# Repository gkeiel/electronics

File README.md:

# Electronics circuits

A repository with codes, schematic diagrams and simulations of electronic circuits. Each project has its own folder.

The following projects are available:
- [voltage difference detector](./voltage_difference_detector)
- [voltage_signal_conditioner](./voltage_signal_conditioner)
- [voltage source inverter 3-phase SPWM](./voltage_source_inverter_3ph_SPWM)

## Voltage difference detector

A printed circuit board (PCB) design for a voltage difference detector between two input voltages, originally developed for voltage source inverters (VSIs) in parallelism applications. Both the schematic design (.sch) and board layout (.brd) were developed in EAGLE software.

<div align="center">

</div>

## Voltage signal conditioner

A printed circuit board (PCB) design for a voltage sensor and signal conditioner, primarily developed for voltage source inverter (VSI) applications. Both the schematic design (.sch) and board layout (.brd) were developed in EAGLE software.

<div align="center">

</div>

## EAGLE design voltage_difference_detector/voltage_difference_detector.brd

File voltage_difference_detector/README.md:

# Voltage difference detector

A printed circuit board (PCB) design for a voltage difference detector between two input voltages, originally developed for voltage source inverters (VSIs) paralleling applications. Both the schematic design (.sch) and board layout (.brd) were developed in EAGLE software.

Being specified for two 127 V sinusoidal inputs, it contains a circuit with a differential amplifier and a comparator. It calculates the instantaneous voltage difference between the inputs, which is proportional to both phase shift and amplitude of the signals, and compares it with an adjustable threshold. If the threshold is exceeded, the comparator activates a relay and a transistor that retains its current state until a reset button is pressed.

<div align="center">

</div>

##

The figures presented in the sequence show stages involved in manufacturing the PCB and its final destination on a panel for VSI control purposes.

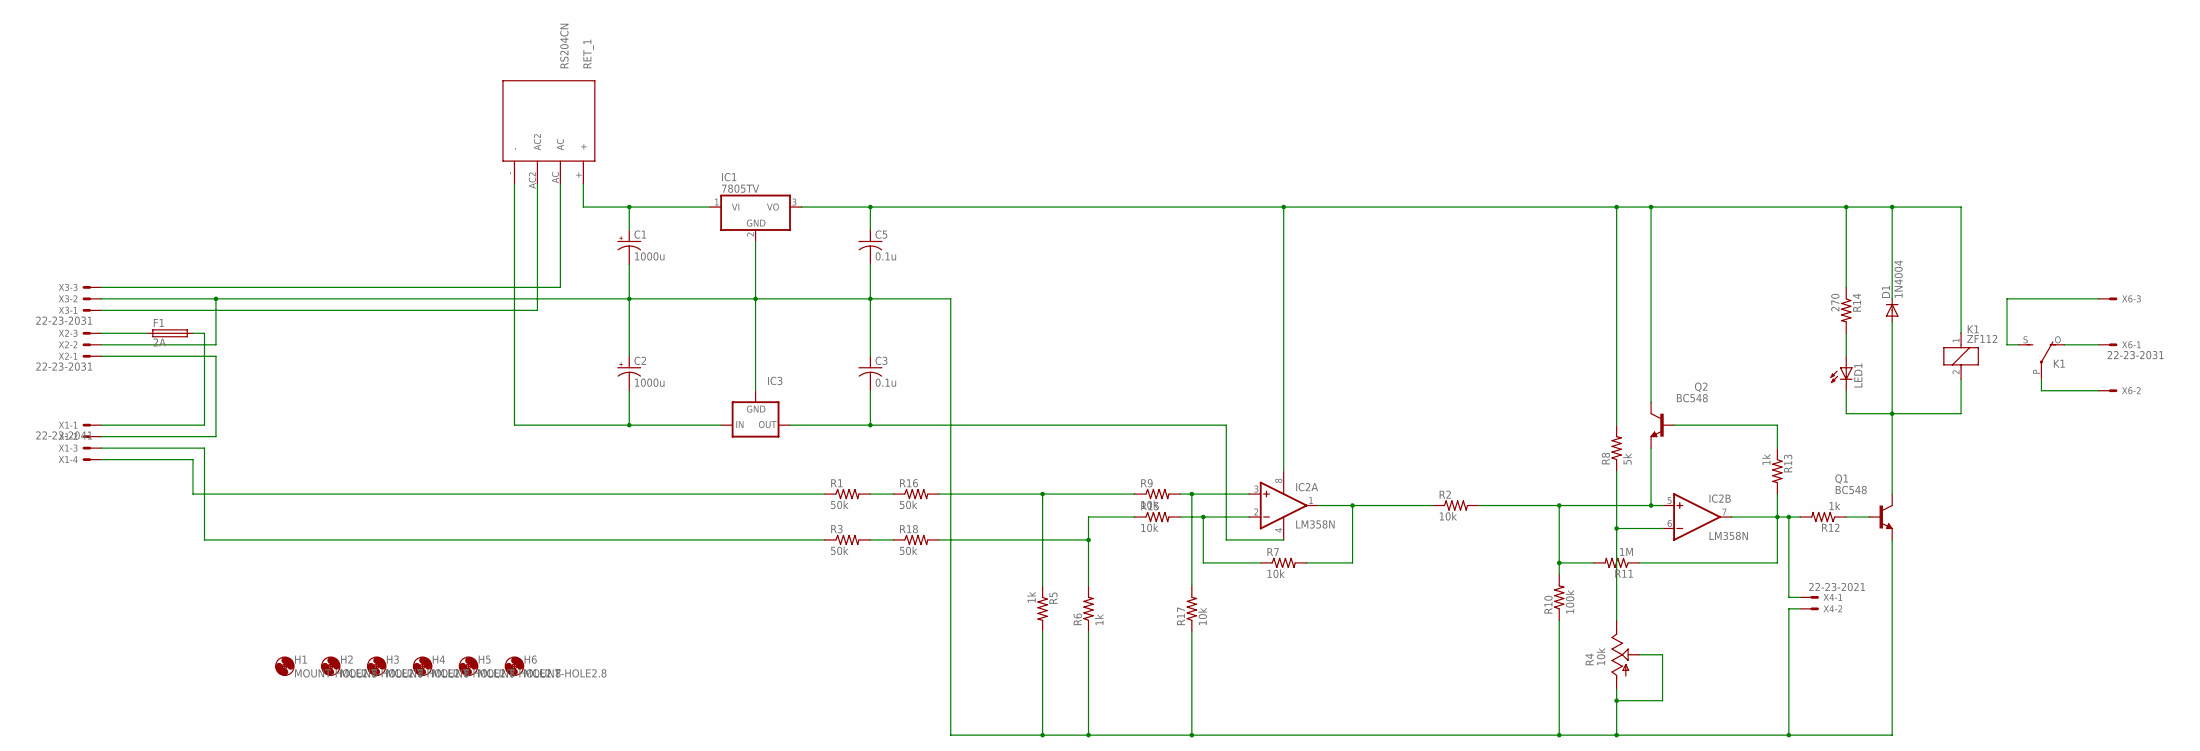
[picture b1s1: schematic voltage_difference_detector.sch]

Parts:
C1, C2: 1000u; E5-10,5
C3, C5: 0.1u; C050-024X044
D1: 1N4004; DO41-10
F1: 2A; SH22,5
H1, H2, H3, H4, H5, H6: MOUNT-HOLE2.8; 2,8
IC1: 7805TV; TO220V
IC2: LM358N; DIL08
IC3: 79XXS
K1: ZF112
LED1: LED3MM
Q1, Q2: BC548; TO92-EBC
R1, R3, R16, R18: 50k; 0204/7
R2, R7, R9, R15, R17: 10k; 0204/7
R4: 10k; RJ9W
R5, R6, R12, R13: 1k; 0204/7
R8: 5k; 0204/7
R10: 100k; 0204/7
R11: 1M; 0204/7
R14: 270; 0204/7
RET_1: RS204CN; SIP
X1: 22-23-2041
X2, X3, X6: 22-23-2031
X4: 22-23-2021

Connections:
GND: C1.-, C2.+, C3.1, C5.2, IC1.2 (GND), IC3.GND, Q1.E, R4.A, R4.S, R5.2, R6.1, R10.1, R17.1, X2.2, X3.2, X4.2
unnamed: C2.-, IC3.IN, RET_1.-
unnamed: IC2.5 (+IN), Q2.E, R2.2, R10.2, R11.2
unnamed: IC2.1 (OUT), R2.1, R7.2
unnamed: RET_1.AC, X3.3
unnamed: R5.1, R9.1, R16.2
unnamed: F1.2, X1.1
unnamed: C1.+, IC1.1 (VI), RET_1.+
unnamed: R1.2, R16.1
unnamed: IC2.2 (-IN), R7.1, R15.2
unnamed: IC2.6 (-IN), R4.E, R8.1
unnamed: IC2.7 (OUT), R11.1, R12.2, R13.2, X4.1
unnamed: Q1.B, R12.1
unnamed: Q2.B, R13.1
unnamed: R6.2, R15.1, R18.2
unnamed: D1.A, K1.2, LED1.K (C), Q1.C
unnamed: R1.1, X1.4
unnamed: R3.1, X1.3
unnamed: RET_1.AC2, X3.1
unnamed: C3.2, IC2.4 (V-), IC3.OUT
unnamed: R3.2, R18.1
unnamed: LED1.A, R14.2
unnamed: X1.2, X2.1
unnamed: K1.O, X6.1
unnamed: K1.P, X6.2
unnamed: K1.S, X6.3
unnamed: IC2.3 (+IN), R9.2, R17.2
unnamed: F1.1, X2.3
VCC: C5.1, D1.C, IC1.3 (VO), IC2.8 (V+), K1.1, Q2.C, R8.2, R14.1

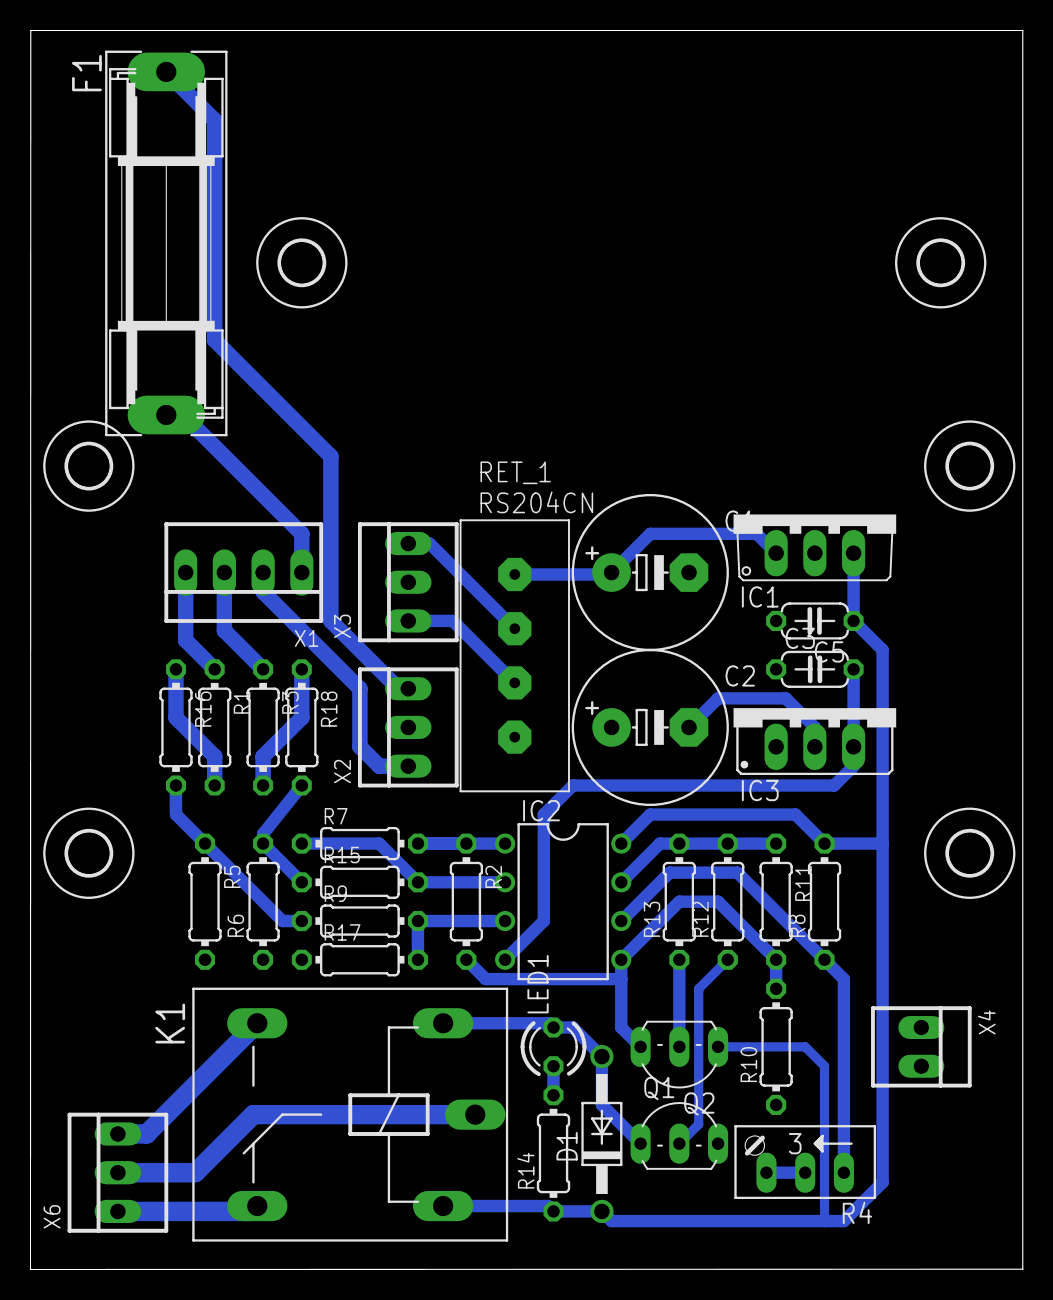
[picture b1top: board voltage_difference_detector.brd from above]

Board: 2 copper layers, 65.1 x 81.3 mm, 43 parts (0 on the bottom side), 29 nets.

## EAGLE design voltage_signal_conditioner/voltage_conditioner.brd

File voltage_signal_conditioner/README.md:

# Voltage signal conditioner

A simple yet functional printed circuit board (PCB) design for a voltage sensor and signal conditioner, primarily developed for voltage source inverter (VSI) applications. Both the schematic design (.sch) and board layout (.brd) were developed in EAGLE software.

Being specified for an 127 V RMS voltage, it accepts a maximum amplitude of 200 V. According to the schematic diagram, it contains a voltage divider at the input with a trimmer for fine adjustment, a Zener limiter to limit voltage arround 10 V, and an isolation amplifier ISO124 integrated circuit (IC) powered with two independent voltage sources. The output has a jumper allowing the selection of RC filtering on the signal.

<div align="center">

</div>

##

The figures presented in the sequence show stages involved in manufacturing the PCB and its final destination on an electirc panel used for control purposes.

<div align="center">

</div>

<div align="center">

</div>

<div align="center">

</div>

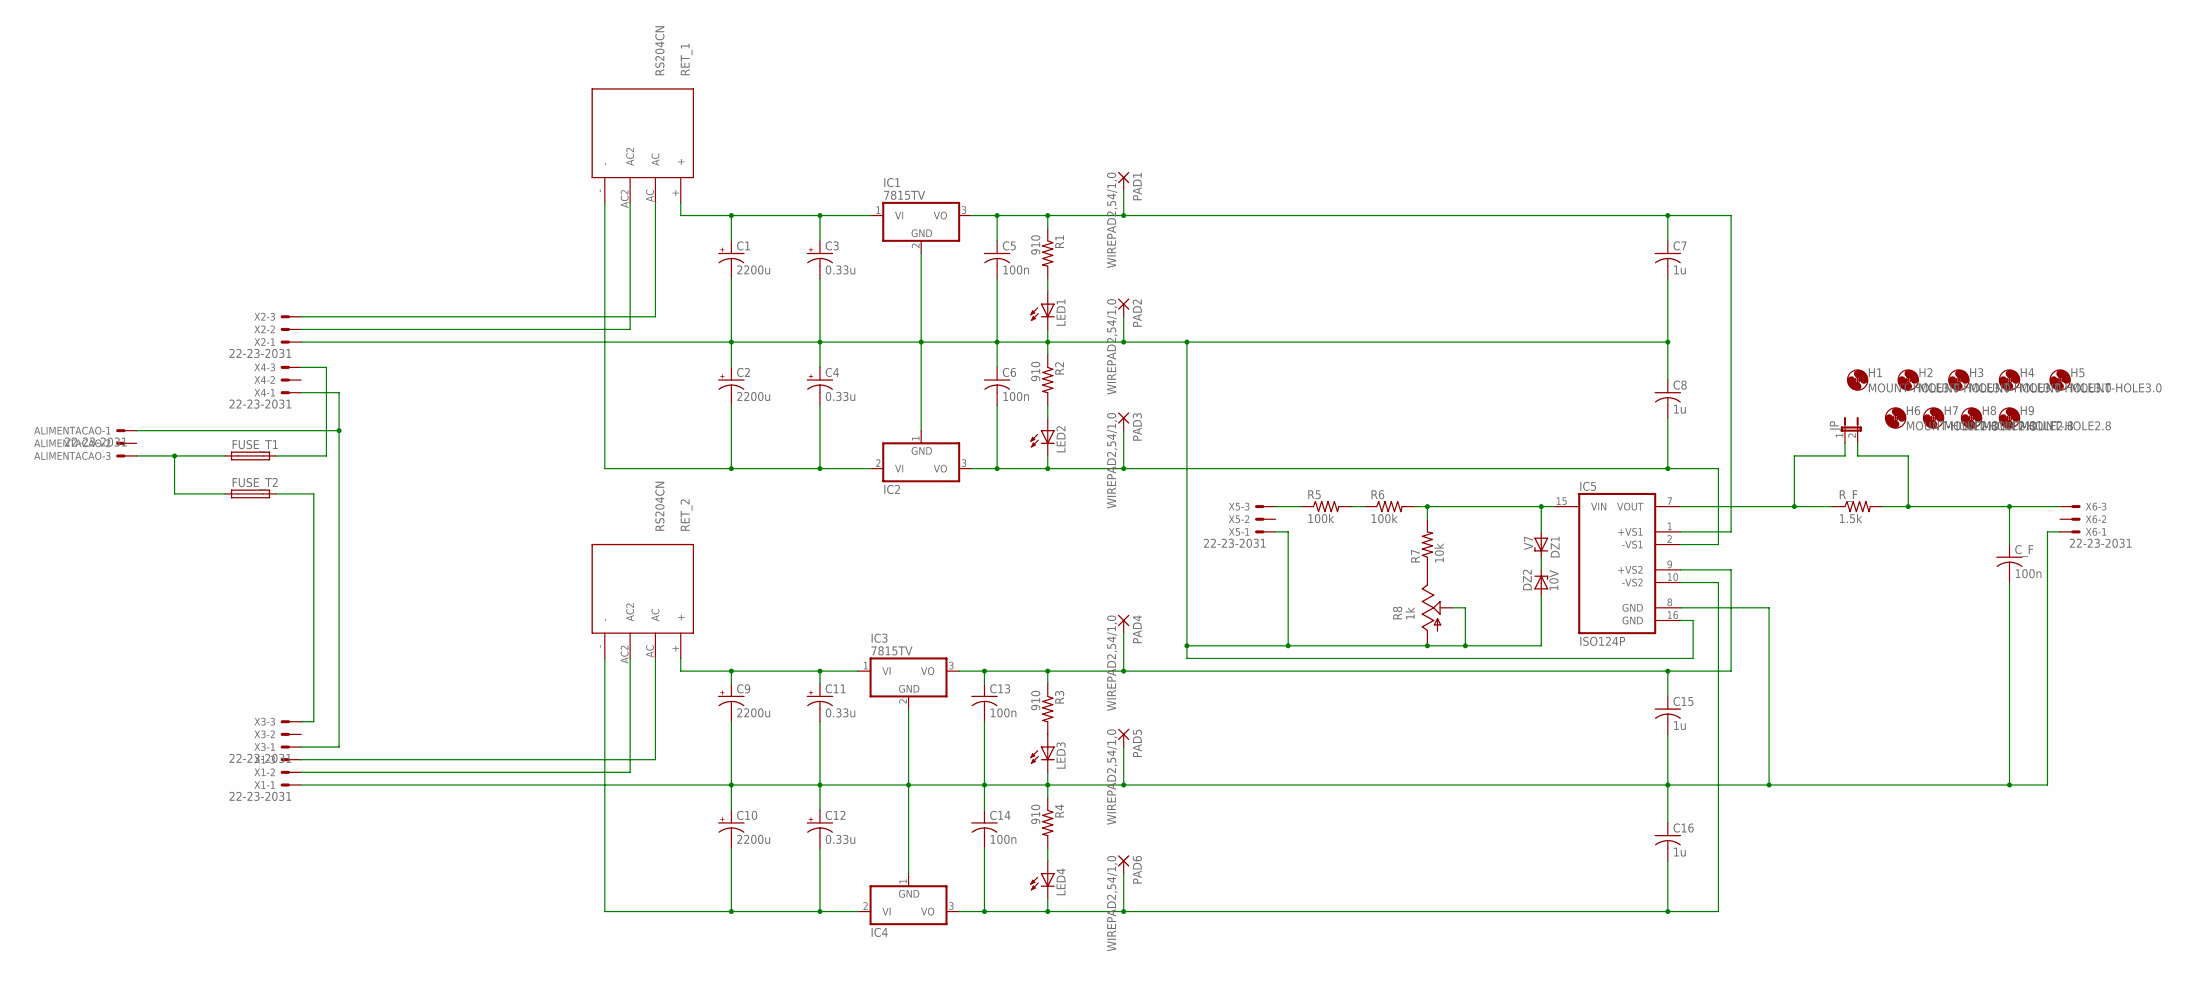
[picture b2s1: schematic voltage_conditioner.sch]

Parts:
ALIMENTACAO: 22-23-2031
C1, C2, C9, C10: 2200u; E5-10,5
C3, C4, C11, C12: 0.33u; E2,5-5
C5, C6, C13, C14: 100n; C050-025X075
C7, C8, C15, C16: 1u; C025-025X050
C_F: 100n; C050-025X075
DZ1: V7; DO35Z10
DZ2: 10V; DO35Z10
FUSE_T1, FUSE_T2: GSH15
H1, H2, H3, H4, H5: MOUNT-HOLE3.0; 3,0
H6, H7, H8, H9: MOUNT-HOLE2.8; 2,8
IC1, IC3: 7815TV; TO220V
IC2, IC4: 7915C; TO220V
IC5: ISO124P; DIL16/8
JP: JP1E; JP1
LED1, LED2, LED3, LED4: LED3MM
PAD1, PAD2, PAD3, PAD4, PAD5, PAD6: WIREPAD2,54/1,0; 2,54/1,0
R1, R2, R3, R4: 910; 0207/7
R5, R6: 100k; 0204/7
R7: 10k; 0204/7
R8: 1k; RS3
RET_1, RET_2: RS204CN; SIP
R_F: 1.5k; 0204/7
X1, X2, X3, X4, X5, X6: 22-23-2031

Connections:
GND_ENTRADA: C1.-, C2.+, C3.-, C4.+, C5.2, C6.1, C7.2, C8.1, DZ2.A, IC1.2 (GND), IC2.1 (GND), IC5.16 (GND), LED1.K (C), PAD2.1, R2.1, R8.A, R8.S, X2.1, X5.1
GND_SAIDA: C9.-, C10.+, C11.-, C12.+, C13.2, C14.1, C15.2, C16.1, C_F.2, IC3.2 (GND), IC4.1 (GND), IC5.8 (GND), LED3.K (C), PAD5.1, R4.1, X1.1, X6.1
unnamed: IC5.7 (VOUT), JP.1, R_F.1
unnamed: FUSE_T2.2, X3.3
unnamed: ALIMENTACAO.3, FUSE_T1.1, FUSE_T2.1
unnamed: FUSE_T1.2, X4.3
unnamed: RET_1.AC, X2.3
unnamed: RET_2.AC, X1.3
unnamed: C1.+, C3.+, IC1.1 (VI), RET_1.+
unnamed: C13.1, C15.1, IC3.3 (VO), IC5.9 (+VS2), PAD4.1, R3.1
unnamed: C2.-, C4.-, IC2.2 (VI), RET_1.-
unnamed: RET_2.AC2, X1.2
unnamed: R5.1, X5.3
unnamed: C9.+, C11.+, IC3.1 (VI), RET_2.+
unnamed: R7.1, R8.E
unnamed: C5.1, C7.1, IC1.3 (VO), IC5.1 (+VS1), PAD1.1, R1.1
unnamed: C10.-, C12.-, IC4.2 (VI), RET_2.-
unnamed: RET_1.AC2, X2.2
unnamed: C14.2, C16.2, IC4.3 (VO), IC5.10 (-VS2), LED4.K (C), PAD6.1
unnamed: R5.2, R6.1
unnamed: DZ1.A, IC5.15 (VIN), R6.2, R7.2
unnamed: LED2.A, R2.2
unnamed: ALIMENTACAO.1, X3.1, X4.1
unnamed: C_F.1, JP.2, R_F.2, X6.3
unnamed: DZ1.C, DZ2.C
unnamed: LED1.A, R1.2
unnamed: LED3.A, R3.2
unnamed: LED4.A, R4.2
Z2: C6.2, C8.2, IC2.3 (VO), IC5.2 (-VS1), LED2.K (C), PAD3.1

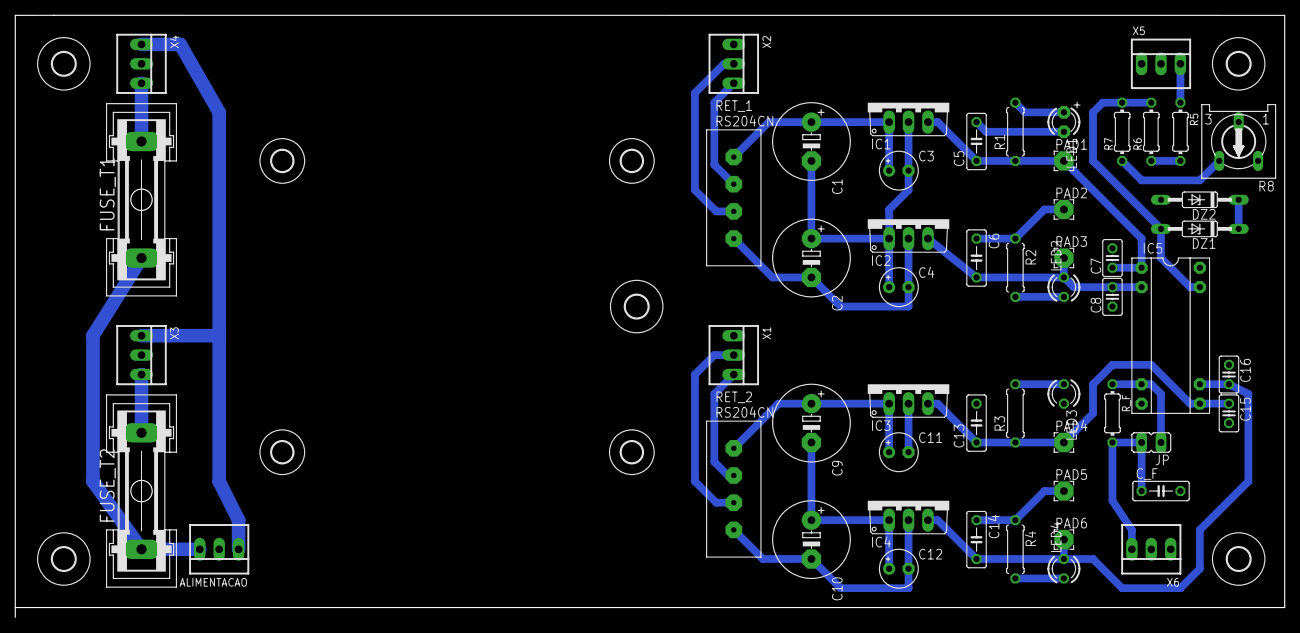
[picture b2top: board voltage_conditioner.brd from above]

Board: 2 copper layers, 166.0 x 78.8 mm, 64 parts (0 on the bottom side), 29 nets.

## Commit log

2025-08-15 v1.0.0
